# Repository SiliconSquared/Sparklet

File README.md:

Welcome to the Sparklet GitHub page, here you'll find our open source designs for the displays, systems, expansion modules, and accessories.

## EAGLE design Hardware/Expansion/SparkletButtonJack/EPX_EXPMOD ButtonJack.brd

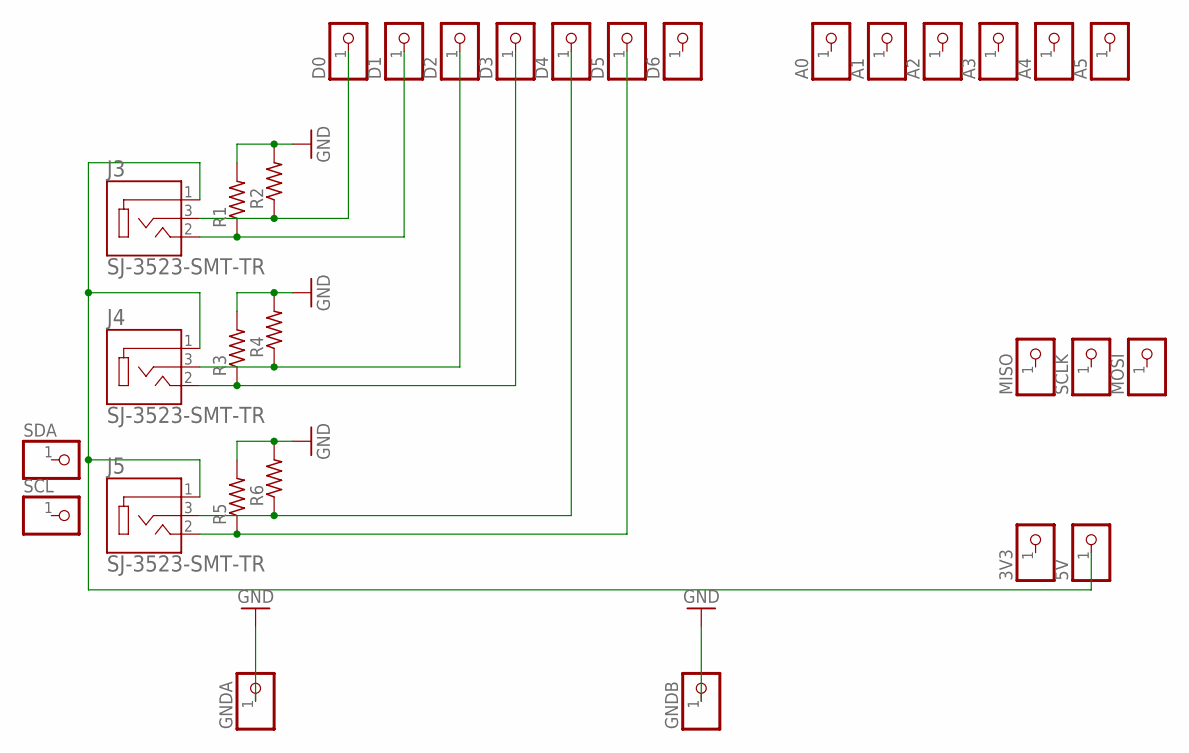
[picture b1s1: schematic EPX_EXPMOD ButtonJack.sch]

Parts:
3V3, 5V: HEADER-1X1ROUND; 1X01_ROUND
A0, A1, A2, A3, A4, A5: HEADER-1X1ROUND; 1X01_ROUND
D0, D1, D2, D3, D4, D5, D6: HEADER-1X1ROUND; 1X01_ROUND
GNDA: HEADER-1X1ROUND; 1X01_ROUND
GNDB: HEADER-1X1ROUND; 1X01_ROUND
J3, J4, J5: SJ-3523-SMT-TR; CUI_SJ-3523-SMT-TR
MISO: HEADER-1X1ROUND; 1X01_ROUND
MOSI: HEADER-1X1ROUND; 1X01_ROUND
R1, R2, R3, R4, R5, R6: R-US_R0603; R0603
SCL: HEADER-1X1ROUND; 1X01_ROUND
SCLK: HEADER-1X1ROUND; 1X01_ROUND
SDA: HEADER-1X1ROUND; 1X01_ROUND

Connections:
GND: GNDA.1, GNDB.1, R1.2, R2.2, R3.2, R4.2, R5.2, R6.2
unnamed: D5.1, J5.2, R5.1
unnamed: D4.1, J5.3, R6.1
unnamed: D3.1, J4.2, R3.1
unnamed: D2.1, J4.3, R4.1
unnamed: D1.1, J3.2, R1.1
unnamed: D0.1, J3.3, R2.1
unnamed: 5V.1, J3.1, J4.1, J5.1

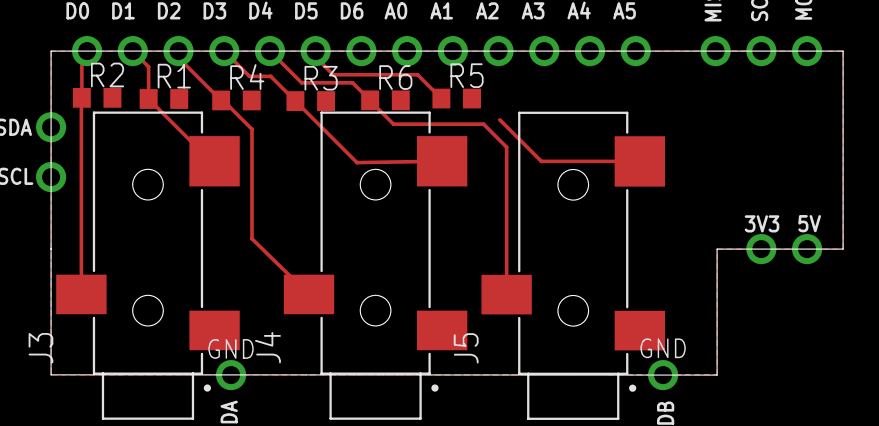
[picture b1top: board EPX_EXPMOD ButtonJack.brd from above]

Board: 2 copper layers, 44.0 x 18.0 mm, 31 parts (0 on the bottom side), 8 nets.

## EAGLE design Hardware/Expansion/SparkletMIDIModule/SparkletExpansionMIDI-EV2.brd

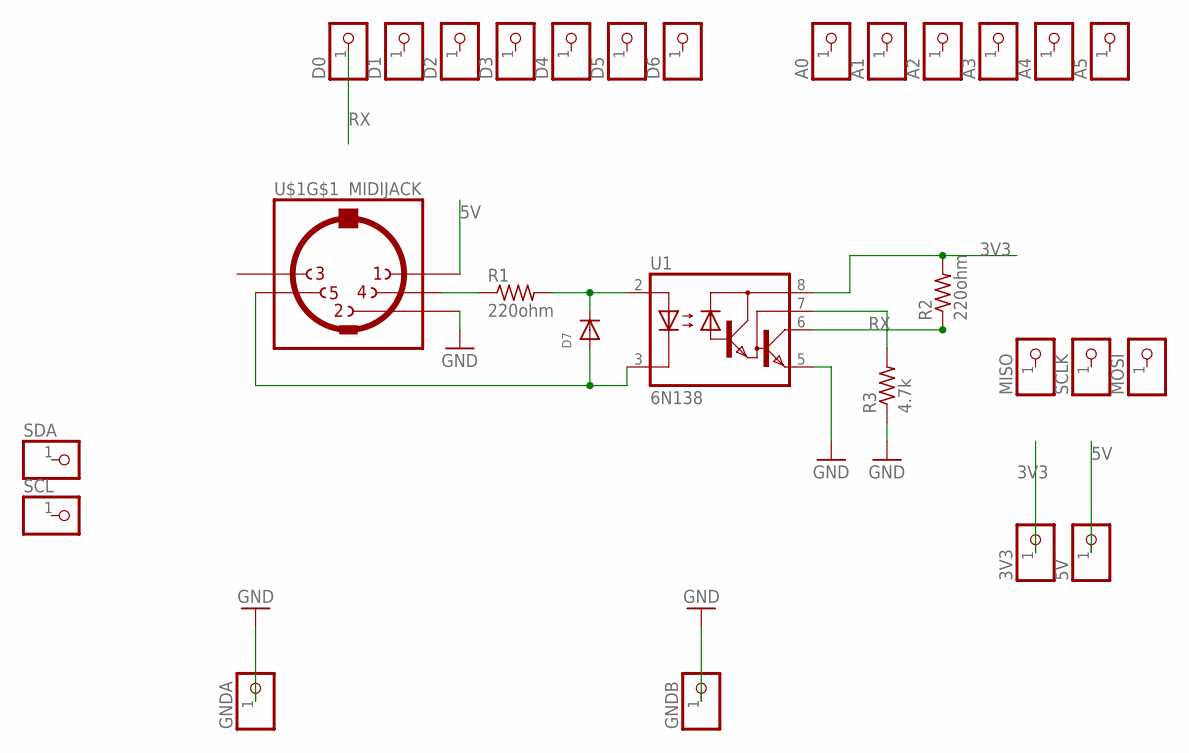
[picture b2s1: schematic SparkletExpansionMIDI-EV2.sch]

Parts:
3V3, 5V: HEADER-1X1ROUND; 1X01_ROUND
A0, A1, A2, A3, A4, A5: HEADER-1X1ROUND; 1X01_ROUND
D0, D1, D2, D3, D4, D5, D6: HEADER-1X1ROUND; 1X01_ROUND
D7: DIODESOD-123; SOD-123
GNDA: HEADER-1X1ROUND; 1X01_ROUND
GNDB: HEADER-1X1ROUND; 1X01_ROUND
MISO: HEADER-1X1ROUND; 1X01_ROUND
MOSI: HEADER-1X1ROUND; 1X01_ROUND
R1, R2: 220ohm; R0603
R3: 4.7k; R0603
SCL: HEADER-1X1ROUND; 1X01_ROUND
SCLK: HEADER-1X1ROUND; 1X01_ROUND
SDA: HEADER-1X1ROUND; 1X01_ROUND
U1: 6N138; DIL08
U$1: MIDIJACK; CP-2350

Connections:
3V3: 3V3.1, R2.2, U1.8 (VCC)
5V: 5V.1, U$1.1
GND: GNDA.1, GNDB.1, R3.1, U1.5 (GND), U$1.2
unnamed: R1.1, U$1.4
unnamed: D7.C, R1.2, U1.2 (A)
unnamed: R3.2, U1.7 (VB)
unnamed: D7.A, U1.3 (C), U$1.5
RX: D0.1, R2.1, U1.6 (VO)

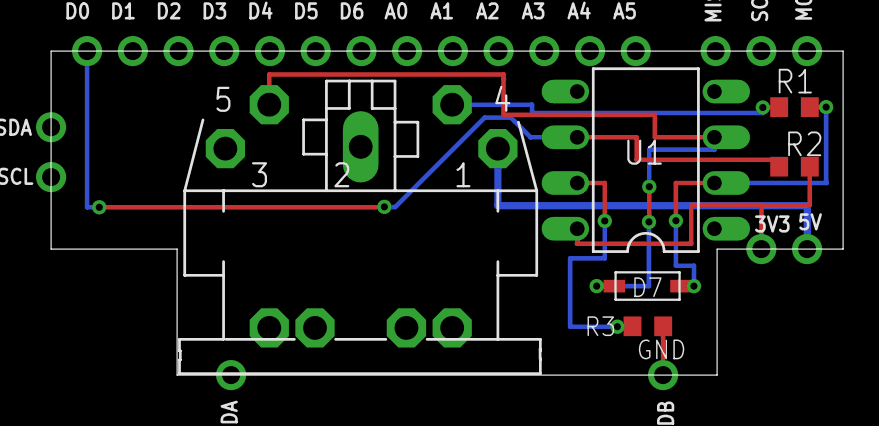
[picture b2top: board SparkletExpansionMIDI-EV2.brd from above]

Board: 2 copper layers, 44.0 x 18.0 mm, 28 parts (0 on the bottom side), 8 nets.

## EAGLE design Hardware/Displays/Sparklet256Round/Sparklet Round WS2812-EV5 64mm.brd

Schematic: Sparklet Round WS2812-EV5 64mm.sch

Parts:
C0: 1uF 10%; C-0402
C1, C2, C3, C4, C5, C6, C7, C8, C9, C10, C11, C12, C13, C14, C15, C16, C17, C18, C19, C20, C21, C22, C23, C24, C25, C26, C27, C28, C29, C30, C31, C32, C33, C34, C35, C36, C37, C38, C39, C40, C41, C42, C43, C44, C45, C46, C47, C48, C49, C50, C51, C52, C53, C54, C55, C56, C57, C58, C59, C60, C61, C62, C63, C64, C65, C66, C67, C68, C69, C70, C71, C72, C73, C74, C75, C76, C77, C78, C79, C80, C81, C82, C83, C84, C85, C86, C87, C88, C89, C90, C91, C92, C93, C94, C95, C96, C97, C98, C99, C100, C101, C102, C103, C104, C105, C106, C107, C108, C109, C110, C111, C112, C113, C114, C115, C116, C117, C118, C119, C120, C121, C122, C123, C124, C125, C126, C127, C128, C129, C130, C131, C132, C133, C134, C135, C136, C137, C138, C139, C140, C141, C142, C143, C144, C145, C146, C147, C148, C149, C150, C151, C152, C153, C154, C155, C156, C157, C158, C159, C160, C161, C162, C163, C164, C165, C166, C167, C168, C169, C170, C171, C172, C173, C174, C175, C176, C177, C178, C179, C180, C181, C182, C183, C184, C185, C186, C187, C188, C189, C190, C191, C192, C193, C194, C195, C196, C197, C198, C199, C200, C201, C202, C203, C204, C205, C206, C207, C208, C209, C210, C211, C212, C213, C214, C215, C216, C217, C218, C219, C220, C221, C222, C223, C224, C225, C226, C227, C228, C229, C230, C231, C232, C233, C234, C235, C236, C237, C238, C239, C240, C241, C242, C243, C244, C245, C246, C247, C248, C249, C250, C251, C252, C253, C254, C255, C256: 100nF; C-0402
FAULT: RED; CHIPLED_0603
GNDA: TPLARGE; TP20RLARGE
GNDB: TPLARGE; TP20RLARGE
JP2: HEADER-1X5ROUND; 1X05_ROUND
R1: 22k; 0603-NO
R2: 220 1%; 0603-NO
R4: 100k; R0402
R6: 10k; R0402
R8: 1k; R0402
RGB1, RGB2, RGB3, RGB4, RGB5, RGB6, RGB7, RGB8, RGB9, RGB10, RGB11, RGB12, RGB13, RGB14, RGB15, RGB16, RGB17, RGB18, RGB19, RGB20, RGB21, RGB22, RGB23, RGB24, RGB25, RGB26, RGB27, RGB28, RGB29, RGB30, RGB31, RGB32, RGB33, RGB34, RGB35, RGB36, RGB37, RGB38, RGB39, RGB40, RGB41, RGB42, RGB43, RGB44, RGB45, RGB46, RGB47, RGB48, RGB49, RGB50, RGB51, RGB52, RGB53, RGB54, RGB55, RGB56, RGB57, RGB58, RGB59, RGB60, RGB61, RGB62, RGB63, RGB64, RGB65, RGB66, RGB67, RGB68, RGB69, RGB70, RGB71, RGB72, RGB73, RGB74, RGB75, RGB76, RGB77, RGB78, RGB79, RGB80, RGB81, RGB82, RGB83, RGB84, RGB85, RGB86, RGB87, RGB88, RGB89, RGB90, RGB91, RGB92, RGB93, RGB94, RGB95, RGB96, RGB97, RGB98, RGB99, RGB100, RGB101, RGB102, RGB103, RGB104, RGB105, RGB106, RGB107, RGB108, RGB109, RGB110, RGB111, RGB112, RGB113, RGB114, RGB115, RGB116, RGB117, RGB118, RGB119, RGB120, RGB121, RGB122, RGB123, RGB124, RGB125, RGB126, RGB127, RGB128, RGB129, RGB130, RGB131, RGB132, RGB133, RGB134, RGB135, RGB136, RGB137, RGB138, RGB139, RGB140, RGB141, RGB142, RGB143, RGB144, RGB145, RGB146, RGB147, RGB148, RGB149, RGB150, RGB151, RGB152, RGB153, RGB154, RGB155, RGB156, RGB157, RGB158, RGB159, RGB160, RGB161, RGB162, RGB163, RGB164, RGB165, RGB166, RGB167, RGB168, RGB169, RGB170, RGB171, RGB172, RGB173, RGB174, RGB175, RGB176, RGB177, RGB178, RGB179, RGB180, RGB181, RGB182, RGB183, RGB184, RGB185, RGB186, RGB187, RGB188, RGB189, RGB190, RGB191, RGB192, RGB193, RGB194, RGB195, RGB196, RGB197, RGB198, RGB199, RGB200, RGB201, RGB202, RGB203, RGB204, RGB205, RGB206, RGB207, RGB208, RGB209, RGB210, RGB211, RGB212, RGB213, RGB214, RGB215, RGB216, RGB217, RGB218, RGB219, RGB220, RGB221, RGB222, RGB223, RGB224, RGB225, RGB226, RGB227, RGB228, RGB229, RGB230, RGB231, RGB232, RGB233, RGB234, RGB235, RGB236, RGB237, RGB238, RGB239, RGB240, RGB241, RGB242, RGB243, RGB244, RGB245, RGB246, RGB247, RGB248, RGB249, RGB250, RGB251, RGB252, RGB253, RGB254, RGB255, RGB256: WS2812-2020; LED_WS2812-2020
U1: NCP380LMUAJAATBG; UDFN-6
U2: SN74LVC1T45; SOT23-6
U3: PRTR5V0U2X; SOT-143B
U$5, U$6, U$7, U$8: HEADERCASTILLATEDPAD; HEADERELONGPAD

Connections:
ENABLE: JP2.2, R6.1, U1.4 (!EN), U$6.1
FLAG: FAULT.C, R4.1, U1.3 (!FLAG)
GND: C0.2, C1.2, C2.2, C3.2, C4.2, C5.2, C6.2, C7.2, C8.2, C9.2, C10.2, C11.2, C12.2, C13.2, C14.2, C15.2, C16.2, C17.2, C18.2, C19.2, C20.2, C21.2, C22.2, C23.2, C24.2, C25.2, C26.2, C27.2, C28.2, C29.2, C30.2, C31.2, C32.2, C33.2, C34.2, C35.2, C36.2, C37.2, C38.2, C39.2, C40.2, C41.2, C42.2, C43.2, C44.2, C45.2, C46.2, C47.2, C48.2, C49.2, C50.2, C51.2, C52.2, C53.2, C54.2, C55.2, C56.2, C57.2, C58.2, C59.2, C60.2, C61.2, C62.2, C63.2, C64.2, C65.2, C66.2, C67.2, C68.2, C69.2, C70.2, C71.2, C72.2, C73.2, C74.2, C75.2, C76.2, C77.2, C78.2, C79.2, C80.2, C81.2, C82.2, C83.2, C84.2, C85.2, C86.2, C87.2, C88.2, C89.2, C90.2, C91.2, C92.2, C93.2, C94.2, C95.2, C96.2, C97.2, C98.2, C99.2, C100.2, C101.2, C102.2, C103.2, C104.2, C105.2, C106.2, C107.2, C108.2, C109.2, C110.2, C111.2, C112.2, C113.2, C114.2, C115.2, C116.2, C117.2, C118.2, C119.2, C120.2, C121.2, C122.2, C123.2, C124.2, C125.2, C126.2, C127.2, C128.2, C129.2, C130.2, C131.2, C132.2, C133.2, C134.2, C135.2, C136.2, C137.2, C138.2, C139.2, C140.2, C141.2, C142.2, C143.2, C144.2, C145.2, C146.2, C147.2, C148.2, C149.2, C150.2, C151.2, C152.2, C153.2, C154.2, C155.2, C156.2, C157.2, C158.2, C159.2, C160.2, C161.2, C162.2, C163.2, C164.2, C165.2, C166.2, C167.2, C168.2, C169.2, C170.2, C171.2, C172.2, C173.2, C174.2, C175.2, C176.2, C177.2, C178.2, C179.2, C180.2, C181.2, C182.2, C183.2, C184.2, C185.2, C186.2, C187.2, C188.2, C189.2, C190.2, C191.2, C192.2, C193.2, C194.2, C195.2, C196.2, C197.2, C198.2, C199.2, C200.2, C201.2, C202.2, C203.2, C204.2, C205.2, C206.2, C207.2, C208.2, C209.2, C210.2, C211.2, C212.2, C213.2, C214.2, C215.2, C216.2, C217.2, C218.2, C219.2, C220.2, C221.2, C222.2, C223.2, C224.2, C225.2, C226.2, C227.2, C228.2, C229.2, C230.2, C231.2, C232.2, C233.2, C234.2, C235.2, C236.2, C237.2, C238.2, C239.2, C240.2, C241.2, C242.2, C243.2, C244.2, C245.2, C246.2, C247.2, C248.2, C249.2, C250.2, C251.2, C252.2, C253.2, C254.2, C255.2, C256.2, GNDA.TP, GNDB.TP, JP2.4, R1.2, R6.2, RGB1.2 (GND), RGB2.2 (GND), RGB3.2 (GND), RGB4.2 (GND), RGB5.2 (GND), RGB6.2 (GND), RGB7.2 (GND), RGB8.2 (GND), RGB9.2 (GND), RGB10.2 (GND), RGB11.2 (GND), RGB12.2 (GND), RGB13.2 (GND), RGB14.2 (GND), RGB15.2 (GND), RGB16.2 (GND), RGB17.2 (GND), RGB18.2 (GND), RGB19.2 (GND), RGB20.2 (GND), RGB21.2 (GND), RGB22.2 (GND), RGB23.2 (GND), RGB24.2 (GND), RGB25.2 (GND), RGB26.2 (GND), RGB27.2 (GND), RGB28.2 (GND), RGB29.2 (GND), RGB30.2 (GND), RGB31.2 (GND), RGB32.2 (GND), RGB33.2 (GND), RGB34.2 (GND), RGB35.2 (GND), RGB36.2 (GND), RGB37.2 (GND), RGB38.2 (GND), RGB39.2 (GND), RGB40.2 (GND), RGB41.2 (GND), RGB42.2 (GND), RGB43.2 (GND), RGB44.2 (GND), RGB45.2 (GND), RGB46.2 (GND), RGB47.2 (GND), RGB48.2 (GND), RGB49.2 (GND), RGB50.2 (GND)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
HOST-PIXDIN: JP2.5, R2.2, U3.3 (IO2), U$8.1
LLIN-PIXDIN: R2.1, U2.4 (B)
unnamed: RGB1.1 (DO), RGB2.3 (DI)
unnamed: RGB2.1 (DO), RGB3.3 (DI)
unnamed: RGB3.1 (DO), RGB4.3 (DI)
unnamed: RGB4.1 (DO), RGB5.3 (DI)
unnamed: RGB5.1 (DO), RGB6.3 (DI)
unnamed: RGB7.1 (DO), RGB8.3 (DI)
unnamed: RGB8.1 (DO), RGB9.3 (DI)
unnamed: RGB9.1 (DO), RGB10.3 (DI)
unnamed: RGB10.1 (DO), RGB11.3 (DI)
unnamed: RGB11.1 (DO), RGB12.3 (DI)
unnamed: RGB12.1 (DO), RGB13.3 (DI)
unnamed: R1.1, U1.2 (ILIM)
unnamed: RGB13.1 (DO), RGB14.3 (DI)
unnamed: RGB14.1 (DO), RGB15.3 (DI)
unnamed: RGB15.1 (DO), RGB16.3 (DI)
unnamed: RGB23.1 (DO), RGB24.3 (DI)
unnamed: RGB6.1 (DO), RGB7.3 (DI)
unnamed: RGB42.1 (DO), RGB43.3 (DI)
unnamed: RGB27.1 (DO), RGB28.3 (DI)
unnamed: RGB18.1 (DO), RGB19.3 (DI)
unnamed: RGB26.1 (DO), RGB27.3 (DI)
unnamed: RGB25.1 (DO), RGB26.3 (DI)
unnamed: RGB24.1 (DO), RGB25.3 (DI)
unnamed: RGB22.1 (DO), RGB23.3 (DI)
unnamed: RGB21.1 (DO), RGB22.3 (DI)
unnamed: RGB20.1 (DO), RGB21.3 (DI)
unnamed: RGB19.1 (DO), RGB20.3 (DI)
unnamed: RGB17.1 (DO), RGB18.3 (DI)
unnamed: RGB16.1 (DO), RGB17.3 (DI)
unnamed: RGB58.1 (DO), RGB59.3 (DI)
unnamed: RGB41.1 (DO), RGB42.3 (DI)
unnamed: RGB40.1 (DO), RGB41.3 (DI)
unnamed: RGB39.1 (DO), RGB40.3 (DI)
unnamed: RGB38.1 (DO), RGB39.3 (DI)
unnamed: RGB37.1 (DO), RGB38.3 (DI)
unnamed: RGB36.1 (DO), RGB37.3 (DI)
unnamed: RGB35.1 (DO), RGB36.3 (DI)
unnamed: RGB34.1 (DO), RGB35.3 (DI)
unnamed: RGB33.1 (DO), RGB34.3 (DI)
unnamed: RGB32.1 (DO), RGB33.3 (DI)
unnamed: RGB31.1 (DO), RGB32.3 (DI)
unnamed: RGB30.1 (DO), RGB31.3 (DI)
unnamed: RGB29.1 (DO), RGB30.3 (DI)
unnamed: RGB28.1 (DO), RGB29.3 (DI)
unnamed: RGB43.1 (DO), RGB44.3 (DI)
unnamed: RGB44.1 (DO), RGB45.3 (DI)
unnamed: RGB45.1 (DO), RGB46.3 (DI)
unnamed: RGB46.1 (DO), RGB47.3 (DI)
unnamed: RGB47.1 (DO), RGB48.3 (DI)
unnamed: RGB48.1 (DO), RGB49.3 (DI)
unnamed: RGB49.1 (DO), RGB50.3 (DI)
unnamed: RGB50.1 (DO), RGB51.3 (DI)
unnamed: RGB51.1 (DO), RGB52.3 (DI)
unnamed: RGB52.1 (DO), RGB53.3 (DI)
unnamed: RGB53.1 (DO), RGB54.3 (DI)
unnamed: RGB54.1 (DO), RGB55.3 (DI)
unnamed: RGB55.1 (DO), RGB56.3 (DI)
unnamed: RGB56.1 (DO), RGB57.3 (DI)
unnamed: RGB75.1 (DO), RGB76.3 (DI)
unnamed: RGB59.1 (DO), RGB60.3 (DI)
unnamed: RGB57.1 (DO), RGB58.3 (DI)
unnamed: RGB60.1 (DO), RGB61.3 (DI)
unnamed: RGB61.1 (DO), RGB62.3 (DI)
unnamed: RGB62.1 (DO), RGB63.3 (DI)
unnamed: RGB63.1 (DO), RGB64.3 (DI)
unnamed: RGB64.1 (DO), RGB65.3 (DI)
unnamed: RGB65.1 (DO), RGB66.3 (DI)
unnamed: RGB66.1 (DO), RGB67.3 (DI)
unnamed: RGB67.1 (DO), RGB68.3 (DI)
unnamed: RGB68.1 (DO), RGB69.3 (DI)
unnamed: RGB69.1 (DO), RGB70.3 (DI)
unnamed: RGB70.1 (DO), RGB71.3 (DI)
unnamed: RGB71.1 (DO), RGB72.3 (DI)
unnamed: RGB72.1 (DO), RGB73.3 (DI)
unnamed: RGB73.1 (DO), RGB74.3 (DI)
unnamed: RGB74.1 (DO), RGB75.3 (DI)
unnamed: RGB121.1 (DO), RGB122.3 (DI)
unnamed: RGB122.1 (DO), RGB123.3 (DI)
unnamed: RGB76.1 (DO), RGB77.3 (DI)
unnamed: RGB77.1 (DO), RGB78.3 (DI)
unnamed: RGB78.1 (DO), RGB79.3 (DI)
unnamed: RGB79.1 (DO), RGB80.3 (DI)
unnamed: RGB80.1 (DO), RGB81.3 (DI)
unnamed: RGB81.1 (DO), RGB82.3 (DI)
unnamed: RGB82.1 (DO), RGB83.3 (DI)
unnamed: RGB83.1 (DO), RGB84.3 (DI)
unnamed: RGB84.1 (DO), RGB85.3 (DI)
unnamed: RGB85.1 (DO), RGB86.3 (DI)
unnamed: RGB86.1 (DO), RGB87.3 (DI)
unnamed: RGB87.1 (DO), RGB88.3 (DI)
unnamed: RGB88.1 (DO), RGB89.3 (DI)
unnamed: RGB89.1 (DO), RGB90.3 (DI)
unnamed: RGB90.1 (DO), RGB91.3 (DI)
unnamed: RGB91.1 (DO), RGB92.3 (DI)
unnamed: RGB123.1 (DO), RGB124.3 (DI)
unnamed: RGB93.1 (DO), RGB94.3 (DI)
unnamed: RGB94.1 (DO), RGB95.3 (DI)
unnamed: RGB95.1 (DO), RGB96.3 (DI)
unnamed: RGB96.1 (DO), RGB97.3 (DI)
unnamed: RGB97.1 (DO), RGB98.3 (DI)
unnamed: RGB98.1 (DO), RGB99.3 (DI)
unnamed: RGB99.1 (DO), RGB100.3 (DI)
unnamed: RGB100.1 (DO), RGB101.3 (DI)
unnamed: RGB101.1 (DO), RGB102.3 (DI)
unnamed: RGB102.1 (DO), RGB103.3 (DI)
unnamed: RGB103.1 (DO), RGB104.3 (DI)
unnamed: RGB104.1 (DO), RGB105.3 (DI)
unnamed: RGB105.1 (DO), RGB106.3 (DI)
unnamed: RGB106.1 (DO), RGB107.3 (DI)
unnamed: RGB107.1 (DO), RGB108.3 (DI)
unnamed: RGB108.1 (DO), RGB109.3 (DI)
unnamed: RGB109.1 (DO), RGB110.3 (DI)
unnamed: RGB198.1 (DO), RGB199.3 (DI)
unnamed: RGB92.1 (DO), RGB93.3 (DI)
unnamed: RGB124.1 (DO), RGB125.3 (DI)
unnamed: RGB111.1 (DO), RGB112.3 (DI)
unnamed: RGB112.1 (DO), RGB113.3 (DI)
unnamed: RGB113.1 (DO), RGB114.3 (DI)
unnamed: RGB114.1 (DO), RGB115.3 (DI)
unnamed: RGB115.1 (DO), RGB116.3 (DI)
unnamed: RGB116.1 (DO), RGB117.3 (DI)
unnamed: RGB117.1 (DO), RGB118.3 (DI)
unnamed: RGB118.1 (DO), RGB119.3 (DI)
unnamed: RGB119.1 (DO), RGB120.3 (DI)
unnamed: RGB120.1 (DO), RGB121.3 (DI)
unnamed: RGB125.1 (DO), RGB126.3 (DI)
unnamed: RGB126.1 (DO), RGB127.3 (DI)
unnamed: RGB127.1 (DO), RGB128.3 (DI)
unnamed: RGB110.1 (DO), RGB111.3 (DI)
unnamed: RGB164.1 (DO), RGB165.3 (DI)
unnamed: RGB214.1 (DO), RGB215.3 (DI)
unnamed: RGB147.1 (DO), RGB148.3 (DI)
unnamed: RGB129.1 (DO), RGB130.3 (DI)
unnamed: RGB130.1 (DO), RGB131.3 (DI)
unnamed: RGB131.1 (DO), RGB132.3 (DI)
unnamed: RGB132.1 (DO), RGB133.3 (DI)
unnamed: RGB133.1 (DO), RGB134.3 (DI)
unnamed: RGB134.1 (DO), RGB135.3 (DI)
unnamed: RGB135.1 (DO), RGB136.3 (DI)
unnamed: RGB136.1 (DO), RGB137.3 (DI)
unnamed: RGB137.1 (DO), RGB138.3 (DI)
unnamed: RGB138.1 (DO), RGB139.3 (DI)
unnamed: RGB139.1 (DO), RGB140.3 (DI)
unnamed: RGB140.1 (DO), RGB141.3 (DI)
unnamed: RGB141.1 (DO), RGB142.3 (DI)
unnamed: RGB142.1 (DO), RGB143.3 (DI)
unnamed: RGB143.1 (DO), RGB144.3 (DI)
unnamed: RGB144.1 (DO), RGB145.3 (DI)
unnamed: RGB145.1 (DO), RGB146.3 (DI)
unnamed: RGB128.1 (DO), RGB129.3 (DI)
unnamed: RGB148.1 (DO), RGB149.3 (DI)
unnamed: RGB149.1 (DO), RGB150.3 (DI)
unnamed: RGB150.1 (DO), RGB151.3 (DI)
unnamed: RGB151.1 (DO), RGB152.3 (DI)
unnamed: RGB152.1 (DO), RGB153.3 (DI)
unnamed: RGB153.1 (DO), RGB154.3 (DI)
unnamed: RGB154.1 (DO), RGB155.3 (DI)
unnamed: RGB155.1 (DO), RGB156.3 (DI)
unnamed: RGB156.1 (DO), RGB157.3 (DI)
unnamed: RGB157.1 (DO), RGB158.3 (DI)
unnamed: RGB158.1 (DO), RGB159.3 (DI)
unnamed: RGB159.1 (DO), RGB160.3 (DI)
unnamed: RGB160.1 (DO), RGB161.3 (DI)
unnamed: RGB161.1 (DO), RGB162.3 (DI)
unnamed: RGB162.1 (DO), RGB163.3 (DI)
unnamed: RGB163.1 (DO), RGB164.3 (DI)
unnamed: RGB146.1 (DO), RGB147.3 (DI)
unnamed: RGB165.1 (DO), RGB166.3 (DI)
unnamed: RGB166.1 (DO), RGB167.3 (DI)
unnamed: RGB167.1 (DO), RGB168.3 (DI)
unnamed: RGB168.1 (DO), RGB169.3 (DI)
unnamed: RGB169.1 (DO), RGB170.3 (DI)
unnamed: RGB170.1 (DO), RGB171.3 (DI)
unnamed: RGB171.1 (DO), RGB172.3 (DI)
unnamed: RGB172.1 (DO), RGB173.3 (DI)
unnamed: RGB173.1 (DO), RGB174.3 (DI)
unnamed: RGB174.1 (DO), RGB175.3 (DI)
unnamed: RGB175.1 (DO), RGB176.3 (DI)
unnamed: RGB176.1 (DO), RGB177.3 (DI)
unnamed: RGB177.1 (DO), RGB178.3 (DI)
unnamed: RGB178.1 (DO), RGB179.3 (DI)
unnamed: RGB179.1 (DO), RGB180.3 (DI)
unnamed: RGB180.1 (DO), RGB181.3 (DI)
unnamed: RGB181.1 (DO), RGB182.3 (DI)
unnamed: RGB230.1 (DO), RGB231.3 (DI)
unnamed: RGB183.1 (DO), RGB184.3 (DI)
unnamed: RGB184.1 (DO), RGB185.3 (DI)
unnamed: RGB185.1 (DO), RGB186.3 (DI)
unnamed: RGB186.1 (DO), RGB187.3 (DI)
unnamed: RGB187.1 (DO), RGB188.3 (DI)
unnamed: RGB188.1 (DO), RGB189.3 (DI)
unnamed: RGB189.1 (DO), RGB190.3 (DI)
unnamed: RGB190.1 (DO), RGB191.3 (DI)
unnamed: RGB191.1 (DO), RGB192.3 (DI)
unnamed: RGB192.1 (DO), RGB193.3 (DI)
unnamed: RGB193.1 (DO), RGB194.3 (DI)
unnamed: RGB194.1 (DO), RGB195.3 (DI)
unnamed: RGB195.1 (DO), RGB196.3 (DI)
unnamed: RGB196.1 (DO), RGB197.3 (DI)
unnamed: RGB197.1 (DO), RGB198.3 (DI)
unnamed: RGB182.1 (DO), RGB183.3 (DI)
unnamed: RGB199.1 (DO), RGB200.3 (DI)
unnamed: RGB200.1 (DO), RGB201.3 (DI)
unnamed: RGB201.1 (DO), RGB202.3 (DI)
unnamed: RGB202.1 (DO), RGB203.3 (DI)
unnamed: RGB203.1 (DO), RGB204.3 (DI)
unnamed: RGB204.1 (DO), RGB205.3 (DI)
unnamed: RGB205.1 (DO), RGB206.3 (DI)
unnamed: RGB206.1 (DO), RGB207.3 (DI)
unnamed: RGB207.1 (DO), RGB208.3 (DI)
unnamed: RGB208.1 (DO), RGB209.3 (DI)
unnamed: RGB209.1 (DO), RGB210.3 (DI)
unnamed: RGB210.1 (DO), RGB211.3 (DI)
unnamed: RGB211.1 (DO), RGB212.3 (DI)
unnamed: RGB212.1 (DO), RGB213.3 (DI)
unnamed: RGB213.1 (DO), RGB214.3 (DI)
unnamed: RGB215.1 (DO), RGB216.3 (DI)
unnamed: RGB216.1 (DO), RGB217.3 (DI)
unnamed: RGB217.1 (DO), RGB218.3 (DI)
unnamed: RGB218.1 (DO), RGB219.3 (DI)
unnamed: RGB219.1 (DO), RGB220.3 (DI)
unnamed: RGB220.1 (DO), RGB221.3 (DI)
unnamed: RGB221.1 (DO), RGB222.3 (DI)
unnamed: RGB222.1 (DO), RGB223.3 (DI)
unnamed: RGB223.1 (DO), RGB224.3 (DI)
unnamed: RGB224.1 (DO), RGB225.3 (DI)
unnamed: RGB225.1 (DO), RGB226.3 (DI)
unnamed: RGB226.1 (DO), RGB227.3 (DI)
unnamed: RGB227.1 (DO), RGB228.3 (DI)
unnamed: RGB231.1 (DO), RGB232.3 (DI)
unnamed: RGB229.1 (DO), RGB230.3 (DI)
unnamed: RGB232.1 (DO), RGB233.3 (DI)
unnamed: RGB233.1 (DO), RGB234.3 (DI)
unnamed: RGB234.1 (DO), RGB235.3 (DI)
unnamed: RGB235.1 (DO), RGB236.3 (DI)
unnamed: RGB236.1 (DO), RGB237.3 (DI)
unnamed: RGB237.1 (DO), RGB238.3 (DI)
unnamed: RGB238.1 (DO), RGB239.3 (DI)
unnamed: RGB239.1 (DO), RGB240.3 (DI)
unnamed: RGB228.1 (DO), RGB229.3 (DI)
unnamed: RGB240.1 (DO), RGB241.3 (DI)
unnamed: FAULT.A, R8.2
unnamed: RGB241.1 (DO), RGB242.3 (DI)
unnamed: RGB242.1 (DO), RGB243.3 (DI)
unnamed: RGB243.1 (DO), RGB244.3 (DI)
unnamed: RGB244.1 (DO), RGB245.3 (DI)
unnamed: RGB245.1 (DO), RGB246.3 (DI)
unnamed: RGB246.1 (DO), RGB247.3 (DI)
unnamed: RGB247.1 (DO), RGB248.3 (DI)
unnamed: RGB248.1 (DO), RGB249.3 (DI)
unnamed: RGB249.1 (DO), RGB250.3 (DI)
unnamed: RGB251.1 (DO), RGB252.3 (DI)
unnamed: RGB252.1 (DO), RGB253.3 (DI)
unnamed: RGB253.1 (DO), RGB254.3 (DI)
unnamed: RGB254.1 (DO), RGB255.3 (DI)
unnamed: RGB255.1 (DO), RGB256.3 (DI)
unnamed: RGB250.1 (DO), RGB251.3 (DI)
PIXDIN: RGB1.3 (DI), U2.3 (A)
VDD: C1.1, C2.1, C3.1, C4.1, C5.1, C6.1, C7.1, C8.1, C9.1, C10.1, C11.1, C12.1, C13.1, C14.1, C15.1, C16.1, C17.1, C18.1, C19.1, C20.1, C21.1, C22.1, C23.1, C24.1, C25.1, C26.1, C27.1, C28.1, C29.1, C30.1, C31.1, C32.1, C33.1, C34.1, C35.1, C36.1, C37.1, C38.1, C39.1, C40.1, C41.1, C42.1, C43.1, C44.1, C45.1, C46.1, C47.1, C48.1, C49.1, C50.1, C51.1, C52.1, C53.1, C54.1, C55.1, C56.1, C57.1, C58.1, C59.1, C60.1, C61.1, C62.1, C63.1, C64.1, C65.1, C66.1, C67.1, C68.1, C69.1, C70.1, C71.1, C72.1, C73.1, C74.1, C75.1, C76.1, C77.1, C78.1, C79.1, C80.1, C81.1, C82.1, C83.1, C84.1, C85.1, C86.1, C87.1, C88.1, C89.1, C90.1, C91.1, C92.1, C93.1, C94.1, C95.1, C96.1, C97.1, C98.1, C99.1, C100.1, C101.1, C102.1, C103.1, C104.1, C105.1, C106.1, C107.1, C108.1, C109.1, C110.1, C111.1, C112.1, C113.1, C114.1, C115.1, C116.1, C117.1, C118.1, C119.1, C120.1, C121.1, C122.1, C123.1, C124.1, C125.1, C126.1, C127.1, C128.1, C129.1, C130.1, C131.1, C132.1, C133.1, C134.1, C135.1, C136.1, C137.1, C138.1, C139.1, C140.1, C141.1, C142.1, C143.1, C144.1, C145.1, C146.1, C147.1, C148.1, C149.1, C150.1, C151.1, C152.1, C153.1, C154.1, C155.1, C156.1, C157.1, C158.1, C159.1, C160.1, C161.1, C162.1, C163.1, C164.1, C165.1, C166.1, C167.1, C168.1, C169.1, C170.1, C171.1, C172.1, C173.1, C174.1, C175.1, C176.1, C177.1, C178.1, C179.1, C180.1, C181.1, C182.1, C183.1, C184.1, C185.1, C186.1, C187.1, C188.1, C189.1, C190.1, C191.1, C192.1, C193.1, C194.1, C195.1, C196.1, C197.1, C198.1, C199.1, C200.1, C201.1, C202.1, C203.1, C204.1, C205.1, C206.1, C207.1, C208.1, C209.1, C210.1, C211.1, C212.1, C213.1, C214.1, C215.1, C216.1, C217.1, C218.1, C219.1, C220.1, C221.1, C222.1, C223.1, C224.1, C225.1, C226.1, C227.1, C228.1, C229.1, C230.1, C231.1, C232.1, C233.1, C234.1, C235.1, C236.1, C237.1, C238.1, C239.1, C240.1, C241.1, C242.1, C243.1, C244.1, C245.1, C246.1, C247.1, C248.1, C249.1, C250.1, C251.1, C252.1, C253.1, C254.1, C255.1, C256.1, RGB1.4 (VDD), RGB2.4 (VDD), RGB3.4 (VDD), RGB4.4 (VDD), RGB5.4 (VDD), RGB6.4 (VDD), RGB7.4 (VDD), RGB8.4 (VDD), RGB9.4 (VDD), RGB10.4 (VDD), RGB11.4 (VDD), RGB12.4 (VDD), RGB13.4 (VDD), RGB14.4 (VDD), RGB15.4 (VDD), RGB16.4 (VDD), RGB17.4 (VDD), RGB18.4 (VDD), RGB19.4 (VDD), RGB20.4 (VDD), RGB21.4 (VDD), RGB22.4 (VDD), RGB23.4 (VDD), RGB24.4 (VDD), RGB25.4 (VDD), RGB26.4 (VDD), RGB27.4 (VDD), RGB28.4 (VDD), RGB29.4 (VDD), RGB30.4 (VDD), RGB31.4 (VDD), RGB32.4 (VDD), RGB33.4 (VDD), RGB34.4 (VDD), RGB35.4 (VDD), RGB36.4 (VDD), RGB37.4 (VDD), RGB38.4 (VDD), RGB39.4 (VDD), RGB40.4 (VDD), RGB41.4 (VDD), RGB42.4 (VDD), RGB43.4 (VDD), RGB44.4 (VDD), RGB45.4 (VDD), RGB46.4 (VDD), RGB47.4 (VDD), RGB48.4 (VDD), RGB49.4 (VDD), RGB50.4 (VDD), RGB51.4 (VDD), RGB52.4 (VDD), RGB53.4 (VDD), RGB54.4 (VDD), RGB55.4 (VDD), RGB56.4 (VDD)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
VHOST: C0.1, JP2.1, R4.2, R8.1, U1.6 (VIN), U$5.1

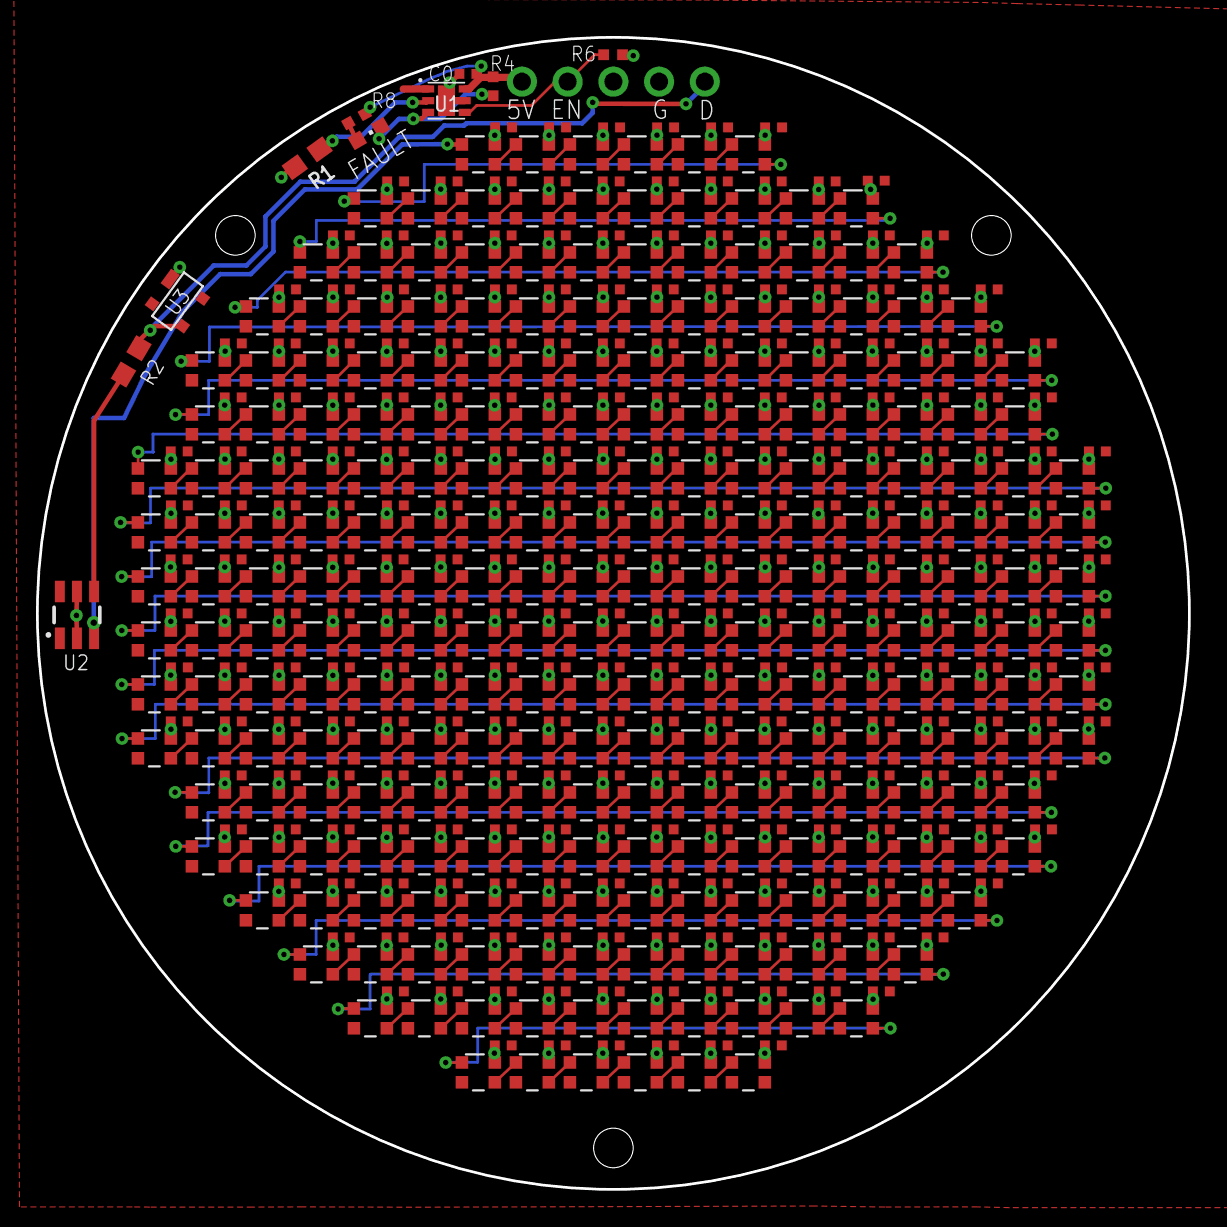
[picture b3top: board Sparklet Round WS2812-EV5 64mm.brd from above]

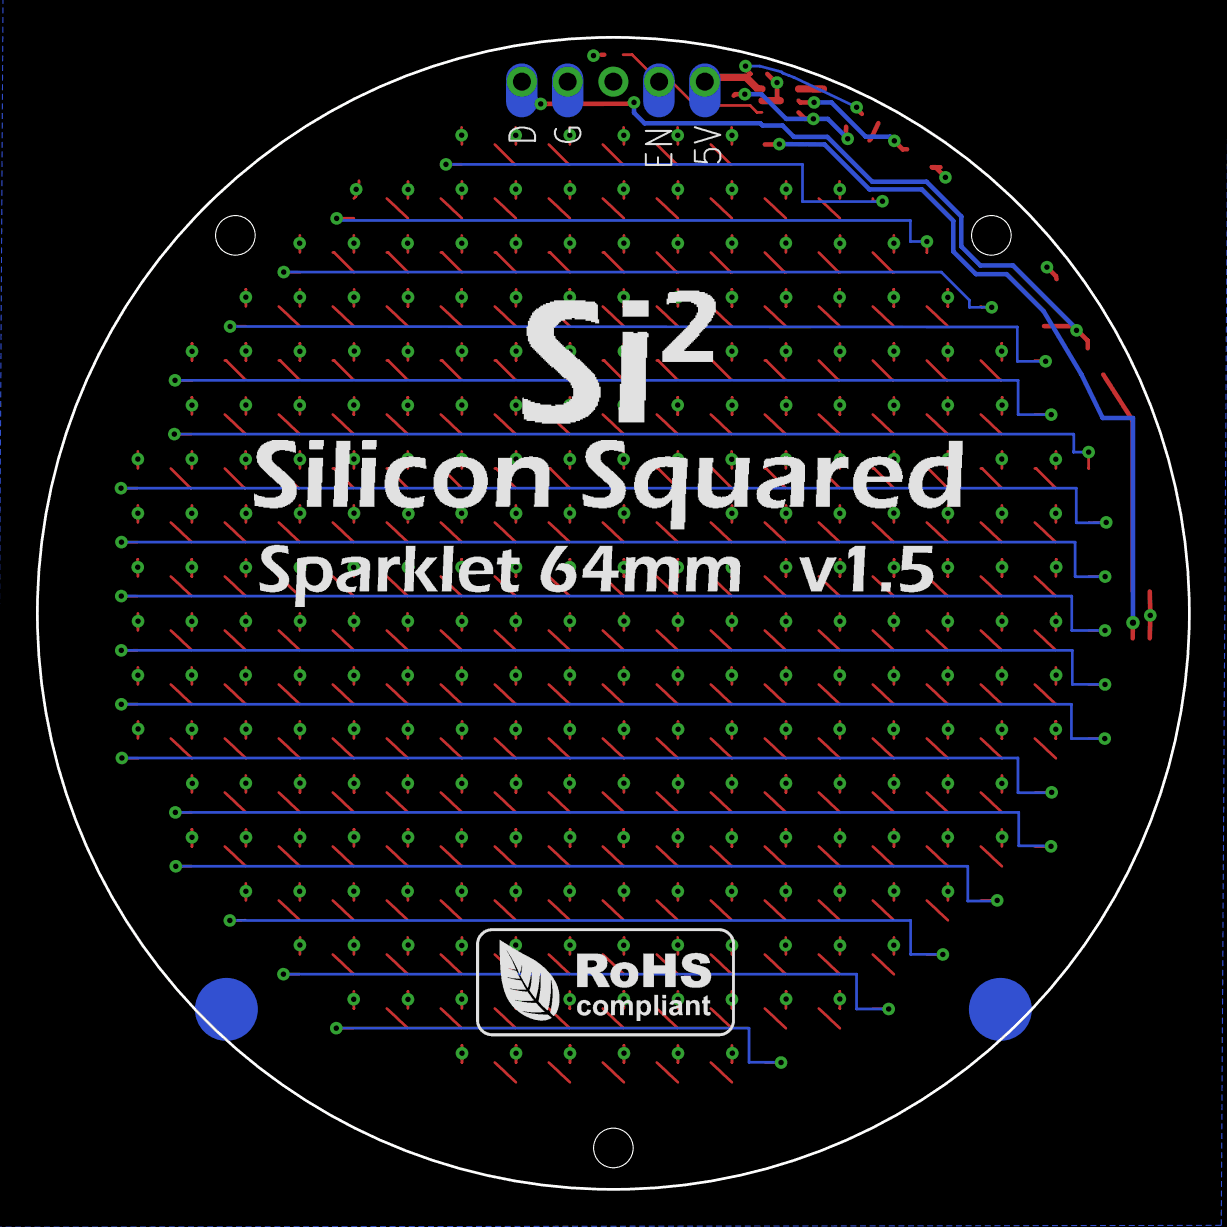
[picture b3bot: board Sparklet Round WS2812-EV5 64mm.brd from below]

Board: 2 copper layers, 64.0 x 64.0 mm, 529 parts (6 on the bottom side), 265 nets.

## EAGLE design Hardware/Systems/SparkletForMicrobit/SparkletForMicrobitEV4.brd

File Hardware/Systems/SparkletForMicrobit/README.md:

# EagleCAD Hardware Design files for Sparklet for micro:bit

# Acknowledgments
The Booster/Charger module design in the SparkletForMicrobit is based on the [Adafruit Powerboost 1000 Charger](https://www.adafruit.com/product/2465)

The amazing engineers at Adafruit created a perfectly optimized module to combine a LiPo charger and 5V booster at a current envelope within the limits of the Sparklet display. Thanks AdaFruit!

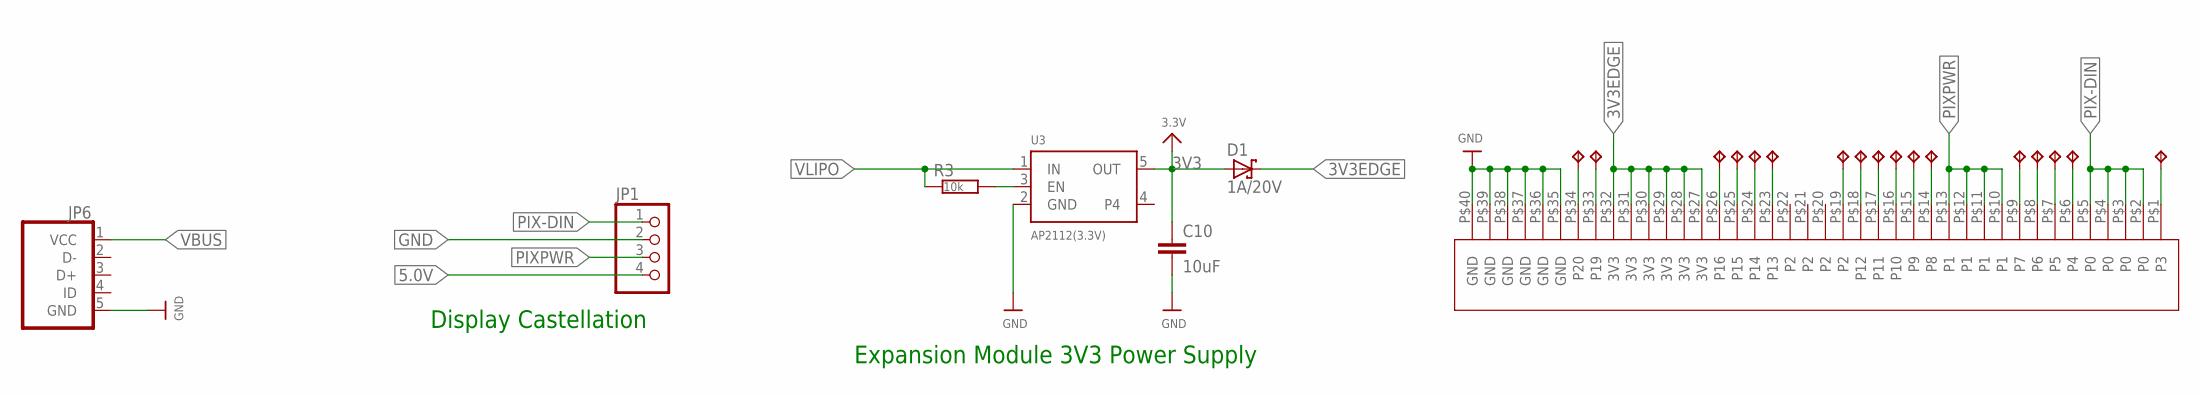
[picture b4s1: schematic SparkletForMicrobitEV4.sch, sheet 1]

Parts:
C10: 10uF; RESC0402_N
D1: 1A/20V; SOD123
JP1: HEADER-1X4ROUND; 1X04_ROUND
JP6: USB-RECEPTABLE; FCI-10103594-0001LF
P1, P2, P3, P4, P5, P6, P7, P8, P9, P10, P11, P12, P13, P14, P15, P16, P17: TPTP15R; TP15R
R3: 10k; RESC0402_N
U3: AP2112(3.3V); SOT23-5
U$2: MIC127-140-001

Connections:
3V3: C10.1, D1.A, U3.5 (OUT)
3V3EDGE: D1.C, U$2.P$27 (3V3), U$2.P$28 (3V3), U$2.P$29 (3V3), U$2.P$30 (3V3), U$2.P$31 (3V3), U$2.P$32 (3V3)
3V3EN: R3.2, U3.3 (EN)
5.0V: JP1.4; also elsewhere on the board
GND: C10.2, JP1.2, JP6.5 (GND), U3.2 (GND), U$2.P$35 (GND), U$2.P$36 (GND), U$2.P$37 (GND), U$2.P$38 (GND), U$2.P$39 (GND), U$2.P$40 (GND); also elsewhere on the board
unnamed: P3.TP, U$2.P$1 (P3)
unnamed: P16.TP, U$2.P$33 (P19)
unnamed: P17.TP, U$2.P$34 (P20)
unnamed: P15.TP, U$2.P$26 (P16)
unnamed: P14.TP, U$2.P$25 (P15)
unnamed: P13.TP, U$2.P$24 (P14)
unnamed: P12.TP, U$2.P$23 (P13)
unnamed: P11.TP, U$2.P$19 (P2)
unnamed: P10.TP, U$2.P$18 (P12)
unnamed: P9.TP, U$2.P$17 (P11)
unnamed: P8.TP, U$2.P$16 (P10)
unnamed: P7.TP, U$2.P$15 (P9)
unnamed: P6.TP, U$2.P$14 (P8)
unnamed: P1.TP, U$2.P$6 (P4)
unnamed: P2.TP, U$2.P$7 (P5)
unnamed: P4.TP, U$2.P$8 (P6)
unnamed: P5.TP, U$2.P$9 (P7)
PIX-DIN: JP1.1, U$2.P$2 (P0), U$2.P$3 (P0), U$2.P$4 (P0), U$2.P$5 (P0)
PIXPWR: JP1.3, U$2.P$10 (P1), U$2.P$11 (P1), U$2.P$12 (P1), U$2.P$13 (P1); also elsewhere on the board
VBUS: JP6.1 (VCC); also elsewhere on the board
VLIPO: R3.1, U3.1 (IN); also elsewhere on the board

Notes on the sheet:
Display Castellation
Expansion Module 3V3 Power Supply

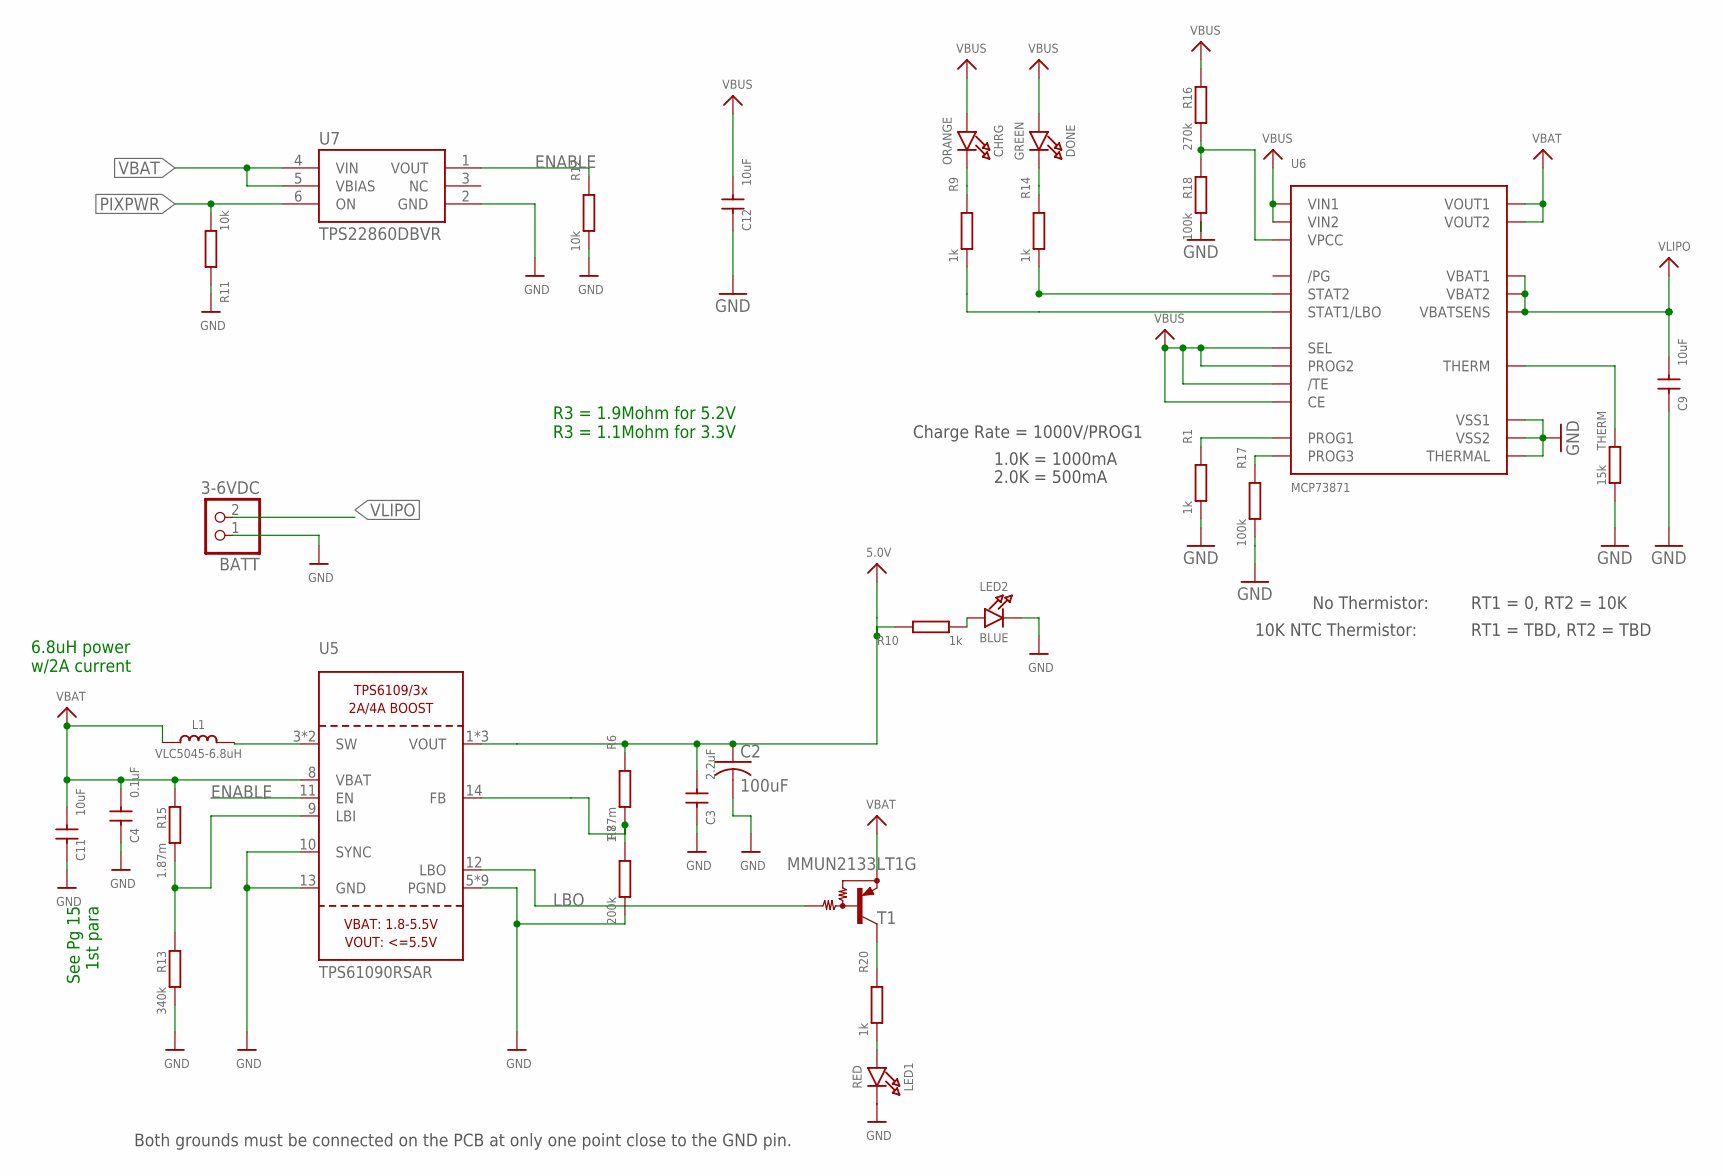
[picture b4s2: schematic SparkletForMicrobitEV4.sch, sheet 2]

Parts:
BATT: 3-6VDC; JSTPH2
C2: 100uF; C1210
C3: 2.2uF; C-0402
C4: 0.1uF; C-0402
C9, C11, C12: 10uF; C-0402
CHRG: ORANGE; CHIPLED_0805_NOOUTLINE
DONE: GREEN; CHIPLED_0805_NOOUTLINE
L1: VLC5045-6.8uH; INDUCTOR_5X5MM_TDK_VLC5045
LED1: RED; CHIPLED_0805_NOOUTLINE
LED2: BLUE; CHIPLED_0805_NOOUTLINE
R1, R9, R10, R14, R20: 1k; R0402
R6, R15: 1.87m; R0402
R7: 200k; R0402
R11, R12: 10k; R0402
R13: 340k; R0402
R16: 270k; R0402
R17, R18: 100k; R0402
T1: MMUN2133LT1G; SC59-BEC
THERM: 15k; R0402
U5: TPS61090RSAR; PVQFN-16
U6: MCP73871; QFN20_4MM
U7: TPS22860DBVR; R-PDSO-G6

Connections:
5.0V: C2.1, C3.1, R6.1, R10.1, U5.1 (VOUT), U5.15 (VOUT), U5.16 (VOUT); also elsewhere on the board
ENABLE: R12.1, U5.11 (EN), U7.1 (VOUT)
GND: BATT.1, C2.2, C3.2, C4.2, C9.2, C11.2, C12.2, LED1.C, LED2.C, R1.2, R7.2, R11.1, R12.2, R13.2, R17.2, R18.2, THERM.2, U5.5 (PGND), U5.6 (PGND), U5.7 (PGND), U5.10 (SYNC), U5.13 (GND), U5.P$18 (PGND), U5.P$19 (PGND), U5.P$20 (PGND), U5.P$21 (PGND), U5.P$22 (PGND), U5.THERMAL (PGND), U6.P$10 (VSS1), U6.P$11 (VSS2), U6.P$21 (THERMAL), U7.2 (GND); also elsewhere on the board
LBO: T1.B, U5.12 (LBO)
unnamed: R13.1, R15.2, U5.9 (LBI)
unnamed: LED1.A, R20.2
unnamed: R6.2, R7.1, U5.14 (FB)
unnamed: R20.1, T1.C
unnamed: LED2.A, R10.2
unnamed: R16.2, R18.1, U6.P$2 (VPCC)
unnamed: R14.2, U6.P$7 (STAT2)
unnamed: R9.2, U6.P$8 (STAT1/LBO)
unnamed: THERM.1, U6.P$5 (THERM)
unnamed: DONE.C, R14.1
unnamed: CHRG.C, R9.1
unnamed: R1.1, U6.P$13 (PROG1)
unnamed: R17.1, U6.P$12 (PROG3)
unnamed: L1.P$2 (2), U5.3 (SW), U5.4 (SW)
PIXPWR: R11.2, U7.6 (ON); also elsewhere on the board
VBAT: C4.1, C11.1, L1.P$1 (1), R15.1, T1.E, U5.8 (VBAT), U6.P$1 (VOUT1), U6.P$20 (VOUT2), U7.4 (VIN), U7.5 (VBIAS)
VBUS: C12.1, CHRG.A, DONE.A, R16.1, U6.P$3 (SEL), U6.P$4 (PROG2), U6.P$9 (/TE), U6.P$17 (CE), U6.P$18 (VIN1), U6.P$19 (VIN2); also elsewhere on the board
VLIPO: BATT.2, C9.1, U6.P$14 (VBAT1), U6.P$15 (VBAT2), U6.P$16 (VBATSENS); also elsewhere on the board

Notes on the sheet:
Both grounds must be connected on the PCB at only one point close to the GND pin.
See Pg 15 1st para
6.8uH power w/2A current
R3 = 1.9Mohm for 5.2V R3 = 1.1Mohm for 3.3V
Charge Rate = 1000V/PROG1
1.0K = 1000mA
2.0K = 500mA
No Thermistor:
10K NTC Thermistor:
RT1 = 0, RT2 = 10K
RT1 = TBD, RT2 = TBD

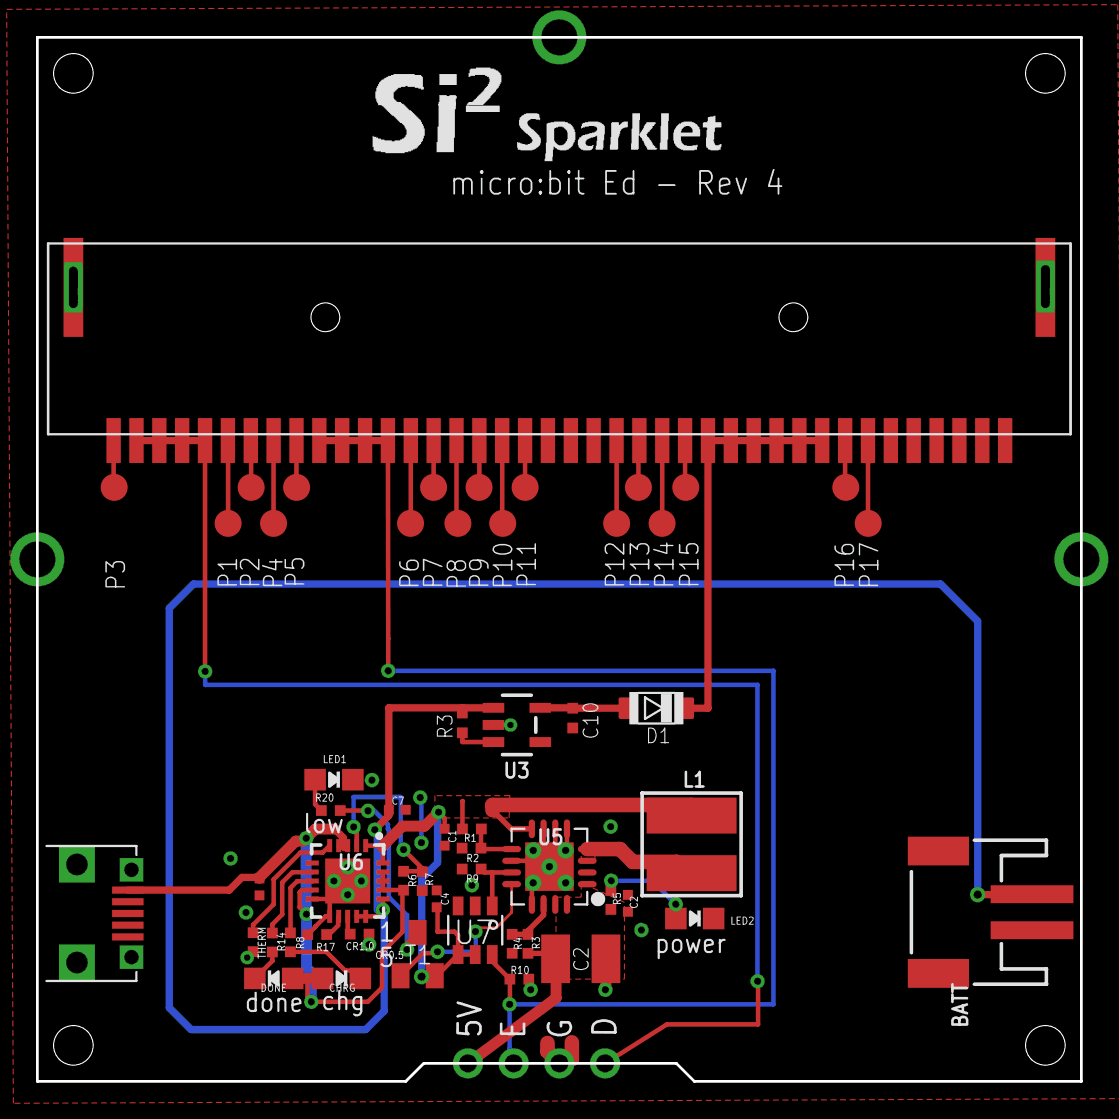
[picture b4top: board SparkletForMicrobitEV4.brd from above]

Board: 2 copper layers, 58.0 x 58.0 mm, 55 parts (0 on the bottom side), 43 nets.

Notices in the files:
parts and their libraries:
microbuilder: This work is placed in the public domain, and may be freely used for commercial and non-commercial work with the following conditions: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
Volks: Creative Commons Attribution-ShareAlike 3.0 Unported (CC BY-SA 3.0), http://creativecommons.org/licenses/by-sa/3.0/.
